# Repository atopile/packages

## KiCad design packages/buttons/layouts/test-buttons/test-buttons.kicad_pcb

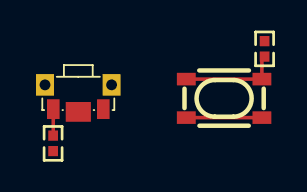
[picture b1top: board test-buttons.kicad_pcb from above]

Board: 2 copper layers, 4 parts (0 on the bottom side), 3 nets.

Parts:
R1, R2: 10kΩ ±1% 62.5mW; R0402
SW1: KEY-SMD_SKTDLDE010
SW2: KEY-SMD_4P-L4.2-W3.2-P2.20-LS4.6

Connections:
btn_horizontal-output: R1.1, SW1.2
btn_vertical-output: R2.1, SW2.3, SW2.4
config_pins[1]-input: SW2.1, SW2.2

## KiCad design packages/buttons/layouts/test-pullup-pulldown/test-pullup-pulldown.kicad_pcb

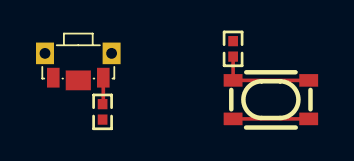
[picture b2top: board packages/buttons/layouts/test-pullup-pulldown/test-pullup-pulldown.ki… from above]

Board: 2 copper layers, 4 parts (0 on the bottom side), 3 nets.

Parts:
R1, R2: 10kΩ ±1% 62.5mW; R0402
SW1: KEY-SMD_SKTDLDE010
SW2: KEY-SMD_4P-L4.2-W3.2-P2.20-LS4.6

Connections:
button-input-input-0: R1.1, SW1.1
button-input-input-1: R2.1, SW2.1, SW2.2
button-output-output-1: SW2.3, SW2.4

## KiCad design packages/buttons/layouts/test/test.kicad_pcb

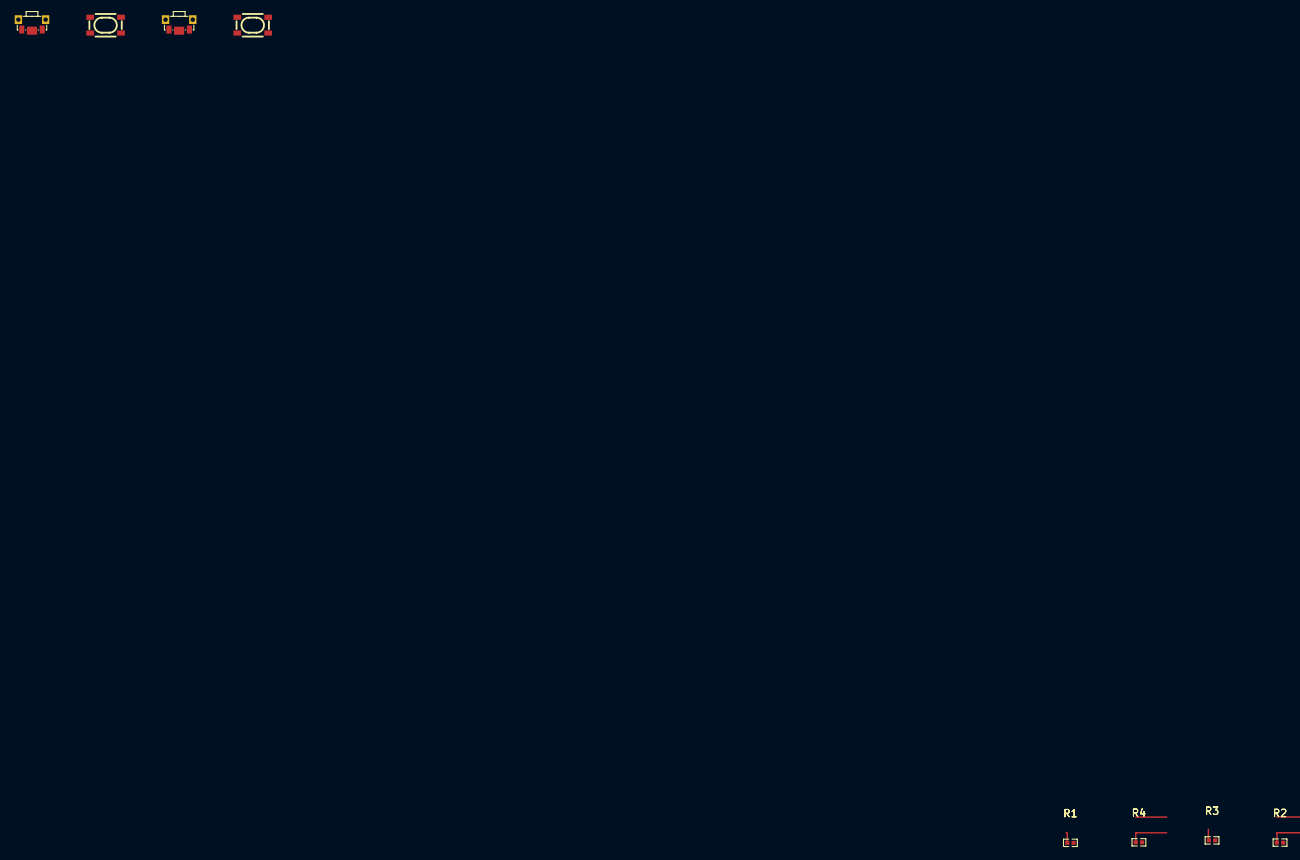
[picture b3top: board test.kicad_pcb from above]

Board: 2 copper layers, 8 parts (0 on the bottom side), 4 nets.

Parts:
R1, R2, R3, R4: 10kΩ ±1% 62.5mW; R0402
SW1, SW3: KEY-SMD_SKTDLDE010
SW2, SW4: KEY-SMD_4P-L4.2-W3.2-P2.20-LS4.6

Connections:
btn_pulldown_vertical.btn.package-line: SW2.1, SW2.2
btn_pulldown_vertical.btn.package-line-1: SW2.3, SW2.4
btn_pullup_vertical.btn.package-line: SW4.1, SW4.2
btn_pullup_vertical.btn.package-line-1: SW4.3, SW4.4

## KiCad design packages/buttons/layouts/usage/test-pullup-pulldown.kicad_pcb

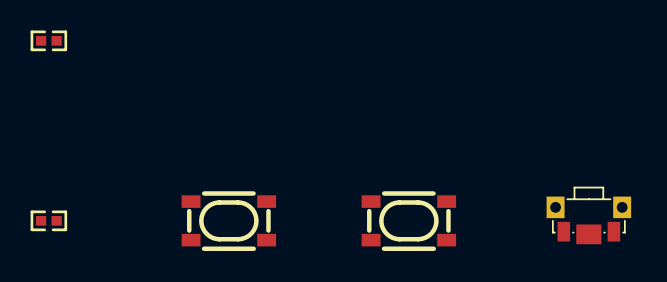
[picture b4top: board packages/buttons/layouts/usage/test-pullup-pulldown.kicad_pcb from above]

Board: 2 copper layers, 5 parts (0 on the bottom side), 6 nets.

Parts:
R1, R2: 10kΩ ±1% 62.5mW; R0402
SW1, SW2: KEY-SMD_4P-L4.2-W3.2-P2.20-LS4.6
SW3: KEY-SMD_SKTDLDE010

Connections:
GND: R1.1, SW3.2
VCC: R2.1, SW2.3, SW2.4
pulldown_signal: R1.2, SW2.1, SW2.2
pullup_signal: R2.2, SW3.1
signal_a: SW1.1, SW1.2
signal_b: SW1.3, SW1.4

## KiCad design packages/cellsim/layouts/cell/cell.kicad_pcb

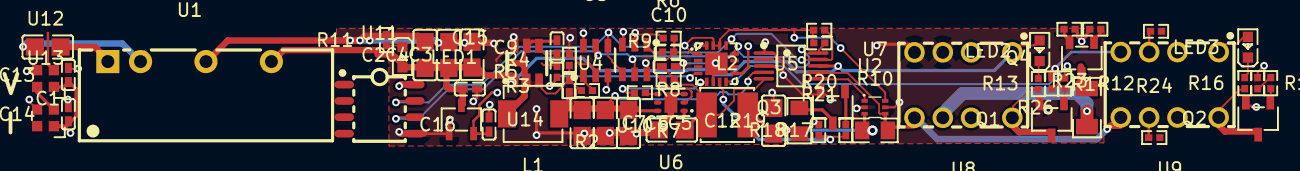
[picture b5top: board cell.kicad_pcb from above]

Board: 4 copper layers, 64 parts (0 on the bottom side), 43 nets.

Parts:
C1: 2.2µF ±10% 25V X7R; C0805
C2, C3, C4, C5, C6, C7, C11, C12: 10µF ±10% 25V X5R; C0805
C9, C13, C14: 100nF ±10% 16V X7R; C0402
C10, C15, C16: 1µF ±10% 16V X5R; C0402
L1: IND-SMD_L4.4-W4.2
L2: IND-SMD_L4.0-W4.0
LED1, LED2, LED3: LED0603-RD
Q1, Q2, Q3, Q4: SOT-23-3_L2.9-W1.6-P1.90-LS2.8-BR
R1, R11, R14: 2kΩ ±1% 62.5mW; R0402
R2: 24kΩ ±1% 62.5mW; R0402
R3: 37.4kΩ ±1% 62.5mW; R0402
R4, R5, R8, R9, R12, R15, R18, R20, R21, R23, R24, R25: 10kΩ ±1% 62.5mW; R0402
R6: 43kΩ ±1% 62.5mW; R0402
R7: 60.4kΩ ±1% 62.5mW; R0402
R10: 100mΩ ±1% 125mW; R0805
R13, R16, R17, R22: 1kΩ ±1% 62.5mW; R0402
R19: 100Ω ±1% 125mW; R0805
R26: 100Ω ±1% 250mW; R1206
U1: PWRM-TH_BXXXXS-2WR3
U2: MSOP-10_L3.0-W3.0-P0.50-LS5.0-BL
U3, U10: SOT-23-6_L2.9-W1.6-P0.95-LS2.8-BL
U4: SOT-23-6_L2.9-W1.6-P0.95-LS2.8-BR
U5: QFN-16_L3.0-W3.0-P0.50-BL-EP1.7
U6: WSON-6_L2.0-W2.0-P0.65-TL-EP
U7: SOT-563_L1.6-W1.2-P0.50-LS1.6-TL
U8, U9: RELAY-TH_HFDXXX
U11: SOIC-8_L4.9-W3.9-P1.27-LS6.0-TL
U12, U13: LED-SMD_4P-L2.0-W2.0-BR
U14: SOT-23-3_L3.0-W1.7-P0.95-LS2.9-BR

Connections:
3V3: C16.1, R20.2, R21.2, U3.3, U3.6, U5.1, U5.14, U5.15, U7.6, U10.3, U11.8, U14.2
3V3_GND: C2.2, C3.2, C4.2, C5.2, C6.2, C7.2, C10.2, C11.2, C12.2, C15.2, C16.2, Q1.2, Q3.2, Q4.2, R4.2, R8.2, R11.2, R13.2, R18.2, R23.2, U1.4, U2.1, U2.3, U3.2, U4.1, U5.6, U5.16, U5.17, U6.3, U6.7, U7.2, U7.5, U8.3, U8.4, U9.4, U10.2, U10.6, U11.5, U14.1
5V: C2.1, C3.1, C4.1, C15.1, LED1.2, LED2.2, U1.6, U2.8, U4.3, U8.1, U14.3
FB: R6.2, R7.2, R8.1, U6.2
SCL: R21.1, U2.10, U3.5, U5.12, U10.5, U11.6
SDA: R20.1, U2.9, U3.4, U5.13, U10.4, U11.7
SW: C9.2, L1.1, U4.2
VBST: C9.1, U4.6
VFB: R2.2, R3.2, R4.1, U4.4
buck-EN: R5.2, U4.5
buck-VOUT: R2.1, U3.1
dmm_relay-gate: Q2.1, R15.2
dmm_relay-gnd: Q2.3, R1.2, U9.8
dmm_relay.indicator_led-cathode: LED3.1, R1.1
external_load-gate: Q4.1, R22.2
gnd: Q4.3, R26.2
gnd-1: R25.1, U9.3
gnd-3: Q3.3, R19.2
gnd-4: C1.2, U1.2
gnd-5: C13.2, C14.2, Q2.2, R16.2, U12.3, U13.3
hv: R10.2, U2.7, U7.4, U8.5, U9.5
hv-1: C1.1, U1.1
hv-2: C12.1, L2.2, R10.1, R19.1, U7.3
hv-3: R24.1, U9.6
hv-4: R26.1, U8.6
hv-6: C5.1, C6.1, C7.1, L1.2, R3.1, U2.4, U6.6
hv-7: C10.1, C11.1, L2.1, R7.1, U2.5, U6.1
hv-8: C13.1, C14.1, LED3.2, U9.1, U12.1, U13.1
isolated_converter.led-cathode: LED1.1, R11.1
ldo-EN: R9.2, U6.4
ldo-VOUT: R6.1, U10.1
line: R5.1, U5.4
line-1: U2.6, U7.1
line-2: R12.1, R13.1, U5.8
line-3: R9.1, U5.5
line-4: R17.1, R18.1, U5.7
line-5: R15.1, R16.1
line-6: R22.1, R23.1, U5.9
line-7: U12.4, U13.2
load_switch-gate: Q3.1, R17.2
output_relay-gate: Q1.1, R12.2
output_relay-gnd: Q1.3, R14.2, U8.8
output_relay.indicator_led-cathode: LED2.1, R14.1
